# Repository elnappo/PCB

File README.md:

# PCB
My collection of custom made PCBs.

## ESP8266-1 BME280 Board

## Packet Radio

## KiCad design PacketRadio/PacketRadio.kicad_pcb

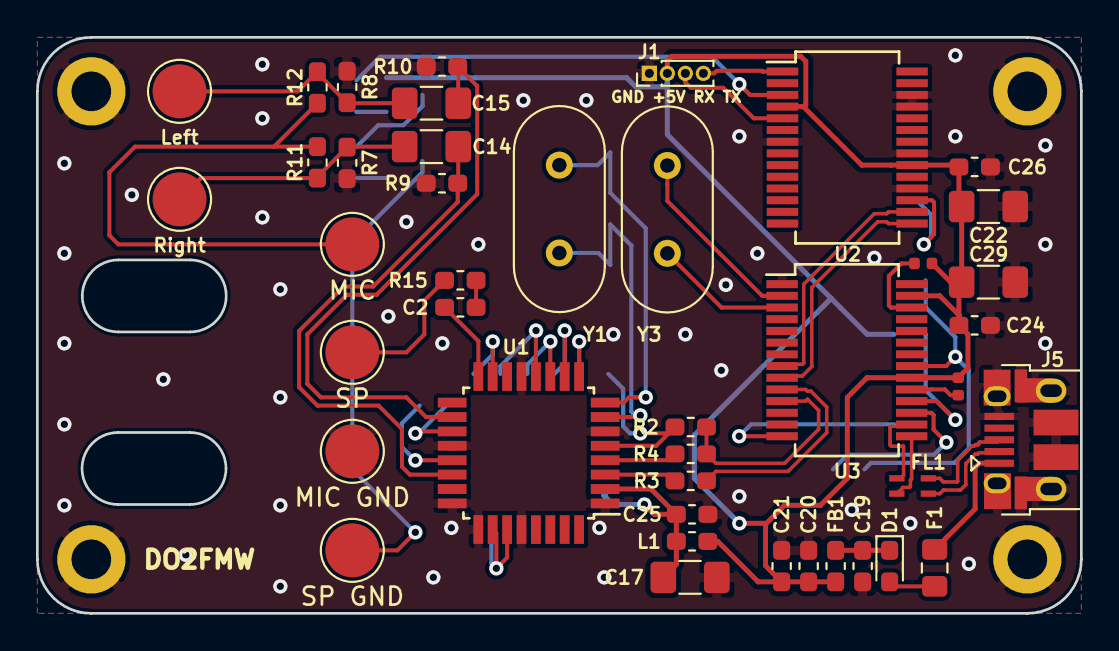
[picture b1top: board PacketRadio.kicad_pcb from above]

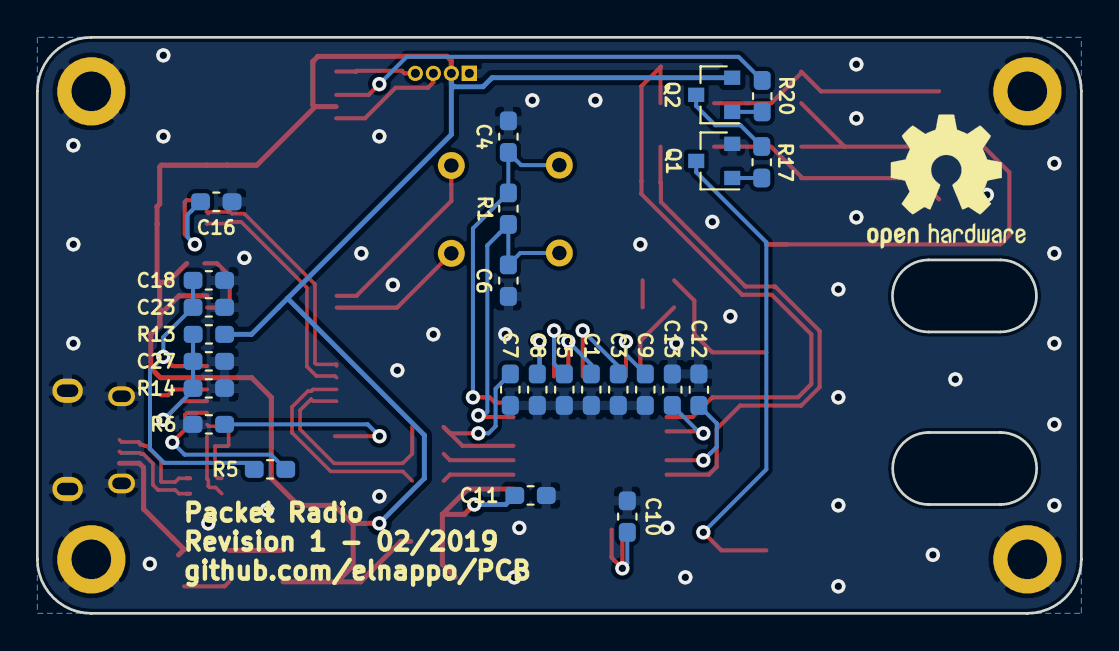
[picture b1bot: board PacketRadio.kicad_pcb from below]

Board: 2 copper layers, 58.0 x 32.0 mm, 71 parts (25 on the bottom side), 51 nets.

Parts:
C1, C2: 3.3 uF; C_0603_1608Metric_Pad1.05x0.95mm_HandSolder
C3, C16, C18, C20, C24, C25, C26, C27: 100 nF; C_0603_1608Metric_Pad1.05x0.95mm_HandSolder
C4, C6: 30 pF; C_0603_1608Metric_Pad1.05x0.95mm_HandSolder
C5, C8: 100 pF; C_0603_1608Metric_Pad1.05x0.95mm_HandSolder
C7, C9, C10, C11, C12, C13: 1 uF; C_0603_1608Metric_Pad1.05x0.95mm_HandSolder
C14, C15: 100 uF; C_1206_3216Metric_Pad1.42x1.75mm_HandSolder
C17, C22, C29: 150 uF; C_1206_3216Metric_Pad1.42x1.75mm_HandSolder
C19: 10 nF; C_0603_1608Metric_Pad1.05x0.95mm_HandSolder
C21, C23: 4.7 uF; C_0603_1608Metric_Pad1.05x0.95mm_HandSolder
D1: D; D_0603_1608Metric_Pad1.05x0.95mm_HandSolder
F1: 500 mA; Fuse_0805_2012Metric_Pad1.15x1.40mm_HandSolder
FB1: Ferrite_Bead; C_0603_1608Metric_Pad1.05x0.95mm_HandSolder
FL1: EMI_Filter_CommonMode; WE-CNSW-HF
H1, H2, H3, H4: MountingHole_Pad; MountingHole_2.2mm_M2_DIN965_Pad
J1: GND +5V RX TX; PinHeader_1x04_P1.00mm_Vertical
J5: USB_B_Micro; USB_Micro-B_Amphenol_10103594-0001LF_Horizontal
L1: 1 uH; L_0603_1608Metric_Pad1.05x0.95mm_HandSolder
Q1: BC847; SOT-23
Q2: BC857; SOT-23
R1: 1M; R_0603_1608Metric_Pad1.05x0.95mm_HandSolder
R2: 1.5k; R_0603_1608Metric_Pad1.05x0.95mm_HandSolder
R3, R4: 22; R_0603_1608Metric_Pad1.05x0.95mm_HandSolder
R5, R13: 10k; R_0603_1608Metric_Pad1.05x0.95mm_HandSolder
R6: 2.7k; R_0603_1608Metric_Pad1.05x0.95mm_HandSolder
R7, R8, R9, R10: 3.3k; R_0603_1608Metric_Pad1.05x0.95mm_HandSolder
R11, R12: 1k; R_0603_1608Metric_Pad1.05x0.95mm_HandSolder
R14: 100k; R_0603_1608Metric_Pad1.05x0.95mm_HandSolder
R15: 0; R_0603_1608Metric_Pad1.05x0.95mm_HandSolder
R16, R18: 0; R_0402_1005Metric
R17, R20: 2.2k; R_0603_1608Metric_Pad1.05x0.95mm_HandSolder
TP1: Right; TestPoint_Pad_D3.0mm
TP2: Left; TestPoint_Pad_D3.0mm
TP3: SP GND; TestPoint_Pad_D3.0mm
TP4: MIC GND; TestPoint_Pad_D3.0mm
TP5: MIC; TestPoint_Pad_D3.0mm
TP6: SP; TestPoint_Pad_D3.0mm
U1: PCM2912APJT; TQFP-32_7x7mm_P0.8mm
U2: FT232RL; SSOP-28_5.3x10.2mm_P0.65mm
U3: XR22404CG28-F; SSOP-28_5.3x10.2mm_P0.65mm
Y1: 6 MHz; Crystal_HC49-4H_Vertical
Y3: 12 MHz; Crystal_HC49-4H_Vertical

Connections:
/D_N: FL1.4, J5.2
/D_P: FL1.2, J5.3
/SP: R15.2, TP6.1
/USB_SC_R_N: R3.2, U1.3
/USB_SC_R_P: R4.2, U1.4
BGND: C1.1, C3.1, C4.1, C5.1, C6.2, C7.1, C8.1, C9.1, C10.1, C11.2, C12.1, C13.2, C16.1, C17.1, C18.2, C19.2, C20.2, C21.1, C22.1, C23.2, C24.2, C25.1, C26.1, C27.1, C29.2, H1.1, H2.1, H3.1, H4.1, J1.1, J5.5, J5.6, Q1.2, R6.1, R7.1, R8.2, R9.1, R10.2, R14.1, TP4.1, U1.1, U1.6, U1.13, U1.20, U1.24, U1.25, U1.28, U2.7, U2.18, U2.21, U2.25, U2.26, U3.1
MIC: R11.1, R12.2, TP5.1
unnamed: C1.2, U1.11
unnamed: C2.2, R15.1
unnamed: C3.2, U1.12
unnamed: C5.2, U1.10
unnamed: C7.2, R2.1, U1.5
unnamed: C8.2, U1.9
unnamed: C9.2, U1.15
unnamed: C14.2, R7.2, R11.2, TP1.1
unnamed: C15.2, R8.1, R12.1, TP2.1
unnamed: C16.2, U2.17
unnamed: C19.1, D1.1, FB1.2
unnamed: C27.2, R13.2, R14.2, U3.18
unnamed: D1.2, F1.1
unnamed: F1.2, J5.1
unnamed: Q1.1, R17.1
unnamed: Q2.1, R20.2
unnamed: Q2.3, R17.2
unnamed: R5.1, U3.17
unnamed: R6.2, U3.14
unnamed: R16.1, U3.19
unnamed: R18.2, U3.26
unnamed: U3.2, Y3.2
unnamed: U3.3, Y3.1
RTS: R20.1, U2.3
RXD: J1.3, U2.5
SP_GND: Q1.3, TP3.1
TXD: J1.4, U2.1
USB_FT_N: U2.16, U3.8
USB_FT_P: U2.15, U3.9
USB_N: FL1.3, U3.15
USB_P: FL1.1, U3.16
USB_SC_N: R3.1, U3.10
USB_SC_P: R2.2, R4.1, U3.11
VBUS: C20.1, C21.2, C22.2, C24.1, C26.2, C29.1, FB1.1, J1.2, L1.1, Q2.2, R13.1, R16.2, R18.1, U2.4, U2.20, U3.20, U3.27
VBUS_SC: C11.1, C17.2, C25.2, L1.2, U1.2
VCC33: C18.1, C23.1, R5.2, U3.21
VCCL: C13.1, U1.19
VCCP: C10.2, U1.26, U1.27
VCCR: C12.2, U1.21
VIN: C2.1, U1.16
VOUTL: C15.1, R10.1, U1.18
VOUTR: C14.1, R9.2, U1.22
XTI: C4.2, R1.2, U1.8, Y1.1
XTO: C6.1, R1.1, U1.7, Y1.2

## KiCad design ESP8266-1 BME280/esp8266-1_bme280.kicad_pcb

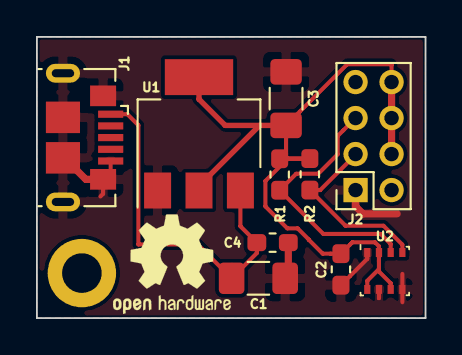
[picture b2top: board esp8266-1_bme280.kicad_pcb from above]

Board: 2 copper layers, 21.6 x 15.6 mm, 11 parts (0 on the bottom side), 5 nets.

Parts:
C1, C3: 10 uF; C_1206_3216Metric_Pad1.42x1.75mm_HandSolder
C2, C4: 100 nF; C_0603_1608Metric_Pad1.05x0.95mm_HandSolder
H1: MountingHole; MountingHole_2.2mm_M2_DIN965_Pad
J1: USB_B_Micro; USB_Micro-B_GCT_USB3076-30-A
J2: Conn_02x04_Odd_Even; PinSocket_2x04_P2.00mm_Vertical
R1, R2: 4.7k; R_0603_1608Metric_Pad1.05x0.95mm_HandSolder
U1: AMS1117-3.3; SOT-223-3_TabPin2
U2: BME280; Bosch_LGA-8_2.5x2.5mm_P0.65mm_ClockwisePinNumbering

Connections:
GND: C1.2, C2.1, C3.2, C4.1, J1.5, J1.6, J2.1, U1.1, U2.1, U2.5, U2.7
unnamed: C1.1, C4.2, J1.1, U1.3
unnamed: C2.2, C3.1, J2.4, J2.6, J2.8, R1.2, R2.2, U1.2, U2.2, U2.6, U2.8
unnamed: J2.3, R2.1, U2.4
unnamed: J2.5, R1.1, U2.3

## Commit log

2019-01-08 Create LICENSE
2019-01-08 Add README.md and .gitignore
2019-01-08 Add ESP8266-1 BME280 Board
2019-01-13 Remove power switch, final design v0.1.0
2019-02-08 Add PacketRadio schematics and pcb
2019-02-08 Update first draft
2019-02-09 Add mounting hole, add BME280 3D modell
2019-04-01 Add common mode choke
2019-04-01 Update 3D modell
2019-05-15 Last fixes before going into production :)
